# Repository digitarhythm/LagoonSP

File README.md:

# TReK Lagoon SP

- TReK Lagoon SP KiCAD Project

[Firmware repository](https://github.com/digitarhythm/vial-qmk/tree/digitarhythm/keyboards/trek/lagoonsp)

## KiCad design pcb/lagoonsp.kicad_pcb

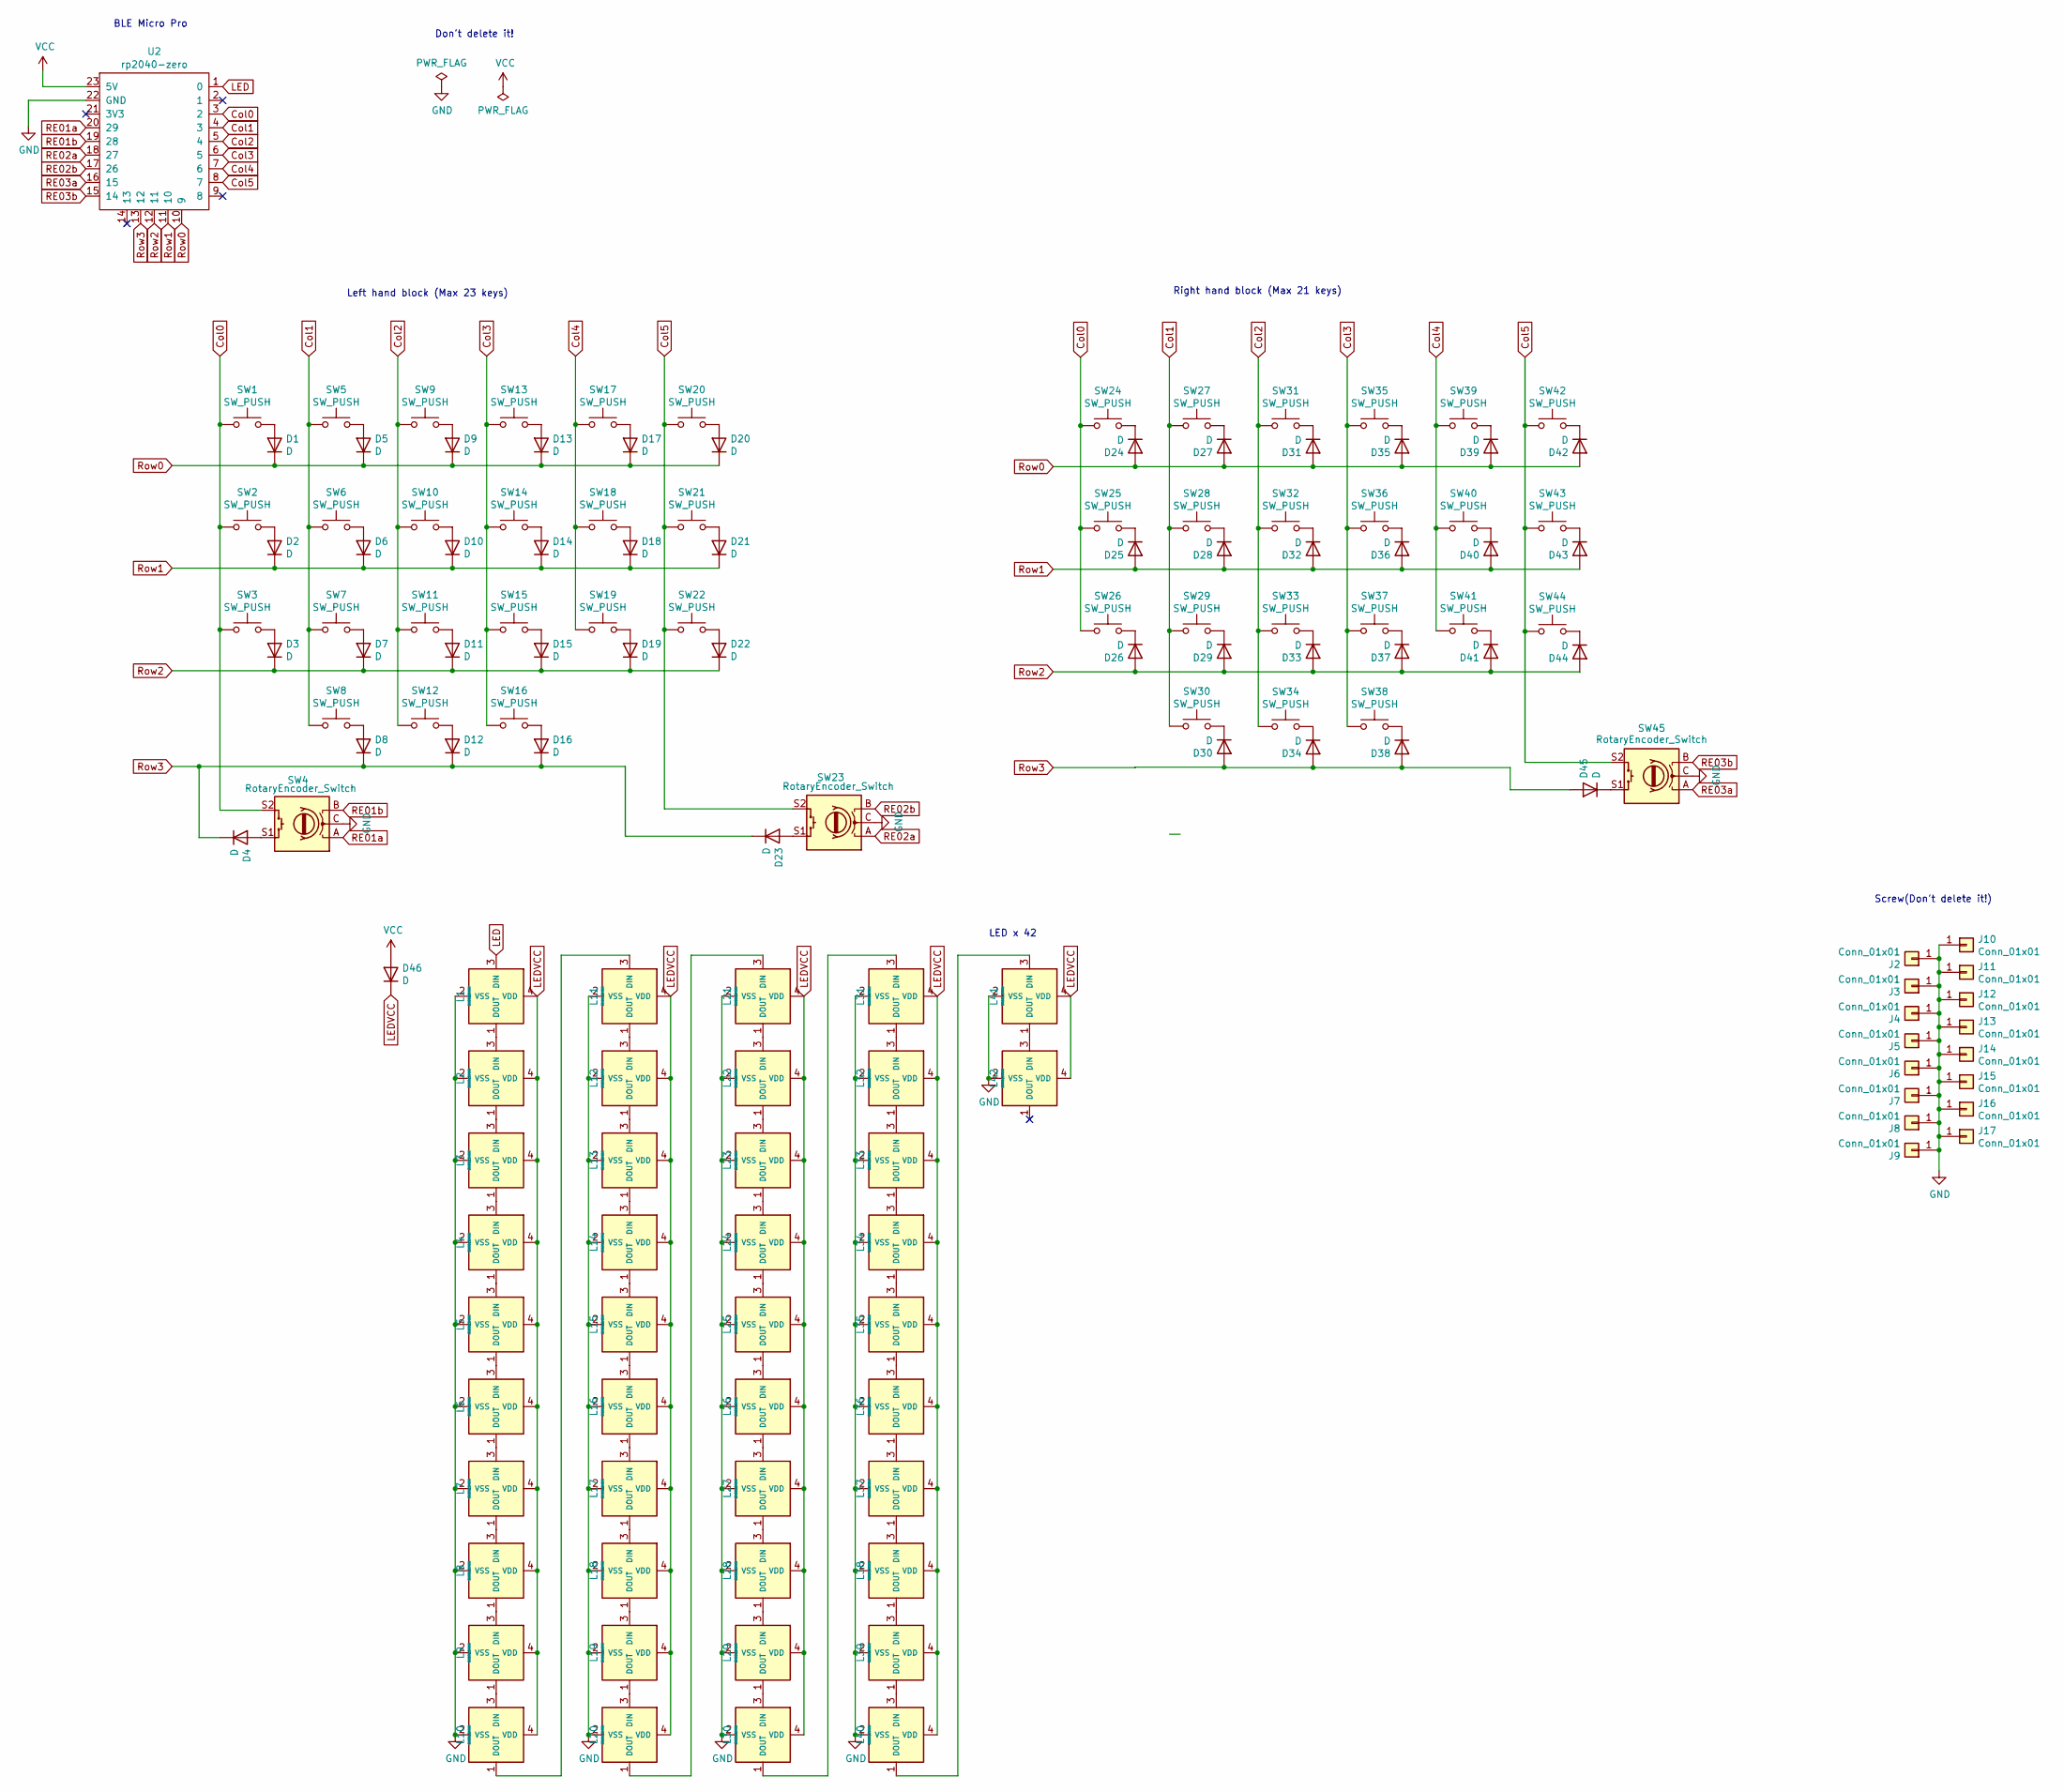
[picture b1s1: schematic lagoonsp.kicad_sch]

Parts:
D1, D2, D3, D4, D5, D6, D7, D8, D9, D10, D11, D12, D13, D14, D15, D16, D17, D18, D19, D20, D21, D22, D23, D24, D25, D26, D27, D28, D29, D30, D31, D32, D33, D34, D35, D36, D37, D38, D39, D40, D41, D42, D43, D44, D45, D46: D; Diode_SMD
J2, J4, J5, J7: Conn_01x01; m2_Spacer_Hole_EdgeCuts
J3, J6: Conn_01x01; m2_Screw_Hole_EdgeCuts
J8, J9, J10, J11, J12, J13, J14, J15, J16, J17: Conn_01x01; m2_Screw_Hole_Fab
L1, L2, L3, L4, L5, L6, L7, L8, L9, L10, L11, L12, L13, L14, L15, L16, L17, L18, L19, L20, L21, L22, L23, L24, L25, L26, L27, L28, L29, L30, L31, L32, L33, L34, L35, L36, L37, L38, L39, L40, L41, L42: SK6812MINI; LED_SK6812MINI-E_BL
SW1, SW2, SW3, SW5, SW6, SW7, SW8, SW9, SW10, SW11, SW12, SW13, SW14, SW15, SW16, SW17, SW18, SW19, SW20, SW21, SW22, SW24, SW25, SW26, SW27, SW28, SW29, SW30, SW31, SW32, SW33, SW34, SW35, SW36, SW37, SW38, SW39, SW40, SW41, SW42, SW43, SW44: SW_PUSH; Lofree_Hotswap_1u
SW4, SW23, SW45: RotaryEncoder_Switch; RotaryEncoder_EC12E
U2: rp2040-zero

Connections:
Col0: SW1.1, SW2.1, SW3.1, SW4.S2, SW24.1, SW25.1, SW26.1, U2.3 (2)
Col1: SW5.1, SW6.1, SW7.1, SW8.1, SW27.1, SW28.1, SW29.1, SW30.1, U2.4 (3)
Col2: SW9.1, SW10.1, SW11.1, SW12.1, SW31.1, SW32.1, SW33.1, SW34.1, U2.5 (4)
Col3: SW13.1, SW14.1, SW15.1, SW16.1, SW35.1, SW36.1, SW37.1, SW38.1, U2.6 (5)
Col4: SW17.1, SW18.1, SW19.1, SW39.1, SW40.1, SW41.1, U2.7 (6)
Col5: SW20.1, SW21.1, SW22.1, SW23.S2, SW42.1, SW43.1, SW44.1, SW45.S2, U2.8 (7)
GND: J2.1, J3.1, J4.1, J5.1, J6.1, J7.1, J8.1, J9.1, J10.1, J11.1, J12.1, J13.1, J14.1, J15.1, J16.1, J17.1, L1.2 (VSS), L2.2 (VSS), L3.2 (VSS), L4.2 (VSS), L5.2 (VSS), L6.2 (VSS), L7.2 (VSS), L8.2 (VSS), L9.2 (VSS), L10.2 (VSS), L11.2 (VSS), L12.2 (VSS), L13.2 (VSS), L14.2 (VSS), L15.2 (VSS), L16.2 (VSS), L17.2 (VSS), L18.2 (VSS), L19.2 (VSS), L20.2 (VSS), L21.2 (VSS), L22.2 (VSS), L23.2 (VSS), L24.2 (VSS), L25.2 (VSS), L26.2 (VSS), L27.2 (VSS), L28.2 (VSS), L29.2 (VSS), L30.2 (VSS), L31.2 (VSS), L32.2 (VSS), L33.2 (VSS), L34.2 (VSS), L35.2 (VSS), L36.2 (VSS), L37.2 (VSS), L38.2 (VSS), L39.2 (VSS), L40.2 (VSS), L41.2 (VSS), L42.2 (VSS), SW4.C, SW23.C, SW45.C, U2.22 (GND)
LED: L1.3 (DIN), U2.1 (0)
LEDVCC: D46.1 (K), L1.4 (VDD), L2.4 (VDD), L3.4 (VDD), L4.4 (VDD), L5.4 (VDD), L6.4 (VDD), L7.4 (VDD), L8.4 (VDD), L9.4 (VDD), L10.4 (VDD), L11.4 (VDD), L12.4 (VDD), L13.4 (VDD), L14.4 (VDD), L15.4 (VDD), L16.4 (VDD), L17.4 (VDD), L18.4 (VDD), L19.4 (VDD), L20.4 (VDD), L21.4 (VDD), L22.4 (VDD), L23.4 (VDD), L24.4 (VDD), L25.4 (VDD), L26.4 (VDD), L27.4 (VDD), L28.4 (VDD), L29.4 (VDD), L30.4 (VDD), L31.4 (VDD), L32.4 (VDD), L33.4 (VDD), L34.4 (VDD), L35.4 (VDD), L36.4 (VDD), L37.4 (VDD), L38.4 (VDD), L39.4 (VDD), L40.4 (VDD), L41.4 (VDD), L42.4 (VDD)
unnamed: D1.2 (A), SW1.2
unnamed: D2.2 (A), SW2.2
unnamed: D3.2 (A), SW3.2
unnamed: D4.2 (A), SW4.S1
unnamed: D5.2 (A), SW5.2
unnamed: D6.2 (A), SW6.2
unnamed: D7.2 (A), SW7.2
unnamed: D8.2 (A), SW8.2
unnamed: D9.2 (A), SW9.2
unnamed: D10.2 (A), SW10.2
unnamed: D11.2 (A), SW11.2
unnamed: D12.2 (A), SW12.2
unnamed: D13.2 (A), SW13.2
unnamed: D14.2 (A), SW14.2
unnamed: D15.2 (A), SW15.2
unnamed: D16.2 (A), SW16.2
unnamed: D17.2 (A), SW17.2
unnamed: D18.2 (A), SW18.2
unnamed: D19.2 (A), SW19.2
unnamed: D20.2 (A), SW20.2
unnamed: D21.2 (A), SW21.2
unnamed: D22.2 (A), SW22.2
unnamed: D23.2 (A), SW23.S1
unnamed: D24.1 (K), SW24.2
unnamed: D25.1 (K), SW25.2
unnamed: D26.1 (K), SW26.2
unnamed: D27.1 (K), SW27.2
unnamed: D28.1 (K), SW28.2
unnamed: D29.1 (K), SW29.2
unnamed: D30.1 (K), SW30.2
unnamed: D31.1 (K), SW31.2
unnamed: D32.1 (K), SW32.2
unnamed: D33.1 (K), SW33.2
unnamed: D34.1 (K), SW34.2
unnamed: D35.1 (K), SW35.2
unnamed: D36.1 (K), SW36.2
unnamed: D37.1 (K), SW37.2
unnamed: D38.1 (K), SW38.2
unnamed: D39.1 (K), SW39.2
unnamed: D40.1 (K), SW40.2
unnamed: D41.1 (K), SW41.2
unnamed: D42.1 (K), SW42.2
unnamed: D43.1 (K), SW43.2
unnamed: D44.1 (K), SW44.2
unnamed: D45.1 (K), SW45.S1
unnamed: L1.1 (DOUT), L2.3 (DIN)
unnamed: L2.1 (DOUT), L3.3 (DIN)
unnamed: L3.1 (DOUT), L4.3 (DIN)
unnamed: L4.1 (DOUT), L5.3 (DIN)
unnamed: L5.1 (DOUT), L6.3 (DIN)
unnamed: L6.1 (DOUT), L7.3 (DIN)
unnamed: L7.1 (DOUT), L8.3 (DIN)
unnamed: L8.1 (DOUT), L9.3 (DIN)
unnamed: L9.1 (DOUT), L10.3 (DIN)
unnamed: L10.1 (DOUT), L11.3 (DIN)
unnamed: L11.1 (DOUT), L12.3 (DIN)
unnamed: L12.1 (DOUT), L13.3 (DIN)
unnamed: L13.1 (DOUT), L14.3 (DIN)
unnamed: L14.1 (DOUT), L15.3 (DIN)
unnamed: L15.1 (DOUT), L16.3 (DIN)
unnamed: L16.1 (DOUT), L17.3 (DIN)
unnamed: L17.1 (DOUT), L18.3 (DIN)
unnamed: L18.1 (DOUT), L19.3 (DIN)
unnamed: L19.1 (DOUT), L20.3 (DIN)
unnamed: L20.1 (DOUT), L21.3 (DIN)
unnamed: L21.1 (DOUT), L22.3 (DIN)
unnamed: L22.1 (DOUT), L23.3 (DIN)
unnamed: L23.1 (DOUT), L24.3 (DIN)
unnamed: L24.1 (DOUT), L25.3 (DIN)
unnamed: L25.1 (DOUT), L26.3 (DIN)
unnamed: L26.1 (DOUT), L27.3 (DIN)
unnamed: L27.1 (DOUT), L28.3 (DIN)
unnamed: L28.1 (DOUT), L29.3 (DIN)
unnamed: L29.1 (DOUT), L30.3 (DIN)
unnamed: L30.1 (DOUT), L31.3 (DIN)
unnamed: L31.1 (DOUT), L32.3 (DIN)
unnamed: L32.1 (DOUT), L33.3 (DIN)
unnamed: L33.1 (DOUT), L34.3 (DIN)
unnamed: L34.1 (DOUT), L35.3 (DIN)
unnamed: L35.1 (DOUT), L36.3 (DIN)
unnamed: L36.1 (DOUT), L37.3 (DIN)
unnamed: L37.1 (DOUT), L38.3 (DIN)
unnamed: L38.1 (DOUT), L39.3 (DIN)
unnamed: L39.1 (DOUT), L40.3 (DIN)
unnamed: L40.1 (DOUT), L41.3 (DIN)
unnamed: L41.1 (DOUT), L42.3 (DIN)
RE01a: SW4.A, U2.20 (29)
RE01b: SW4.B, U2.19 (28)
RE02a: SW23.A, U2.18 (27)
RE02b: SW23.B, U2.17 (26)
RE03a: SW45.A, U2.16 (15)
RE03b: SW45.B, U2.15 (14)
Row0: D1.1 (K), D5.1 (K), D9.1 (K), D13.1 (K), D17.1 (K), D20.1 (K), D24.2 (A), D27.2 (A), D31.2 (A), D35.2 (A), D39.2 (A), D42.2 (A), U2.10 (9)
Row1: D2.1 (K), D6.1 (K), D10.1 (K), D14.1 (K), D18.1 (K), D21.1 (K), D25.2 (A), D28.2 (A), D32.2 (A), D36.2 (A), D40.2 (A), D43.2 (A), U2.11 (10)
Row2: D3.1 (K), D7.1 (K), D11.1 (K), D15.1 (K), D19.1 (K), D22.1 (K), D26.2 (A), D29.2 (A), D33.2 (A), D37.2 (A), D41.2 (A), D44.2 (A), U2.12 (11)
Row3: D4.1 (K), D8.1 (K), D12.1 (K), D16.1 (K), D23.1 (K), D30.2 (A), D34.2 (A), D38.2 (A), D45.2 (A), U2.13 (12)
VCC: D46.2 (A), U2.23 (5V)

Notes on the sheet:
Left hand block (Max 23 keys)
Screw(Don't delete it!)
Don't delete it!
Right hand block (Max 21 keys)
LED x 42
BLE Micro Pro

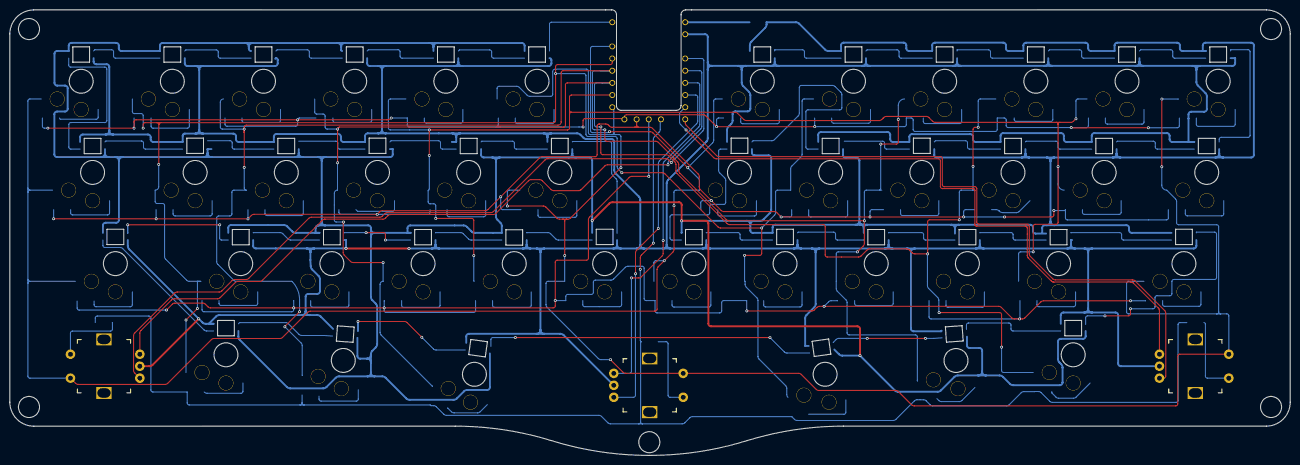
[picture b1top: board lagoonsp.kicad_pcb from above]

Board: 2 copper layers, 267.5 x 93.1 mm, 140 parts (1 on the bottom side), 106 nets.

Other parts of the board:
G000: LOGO
